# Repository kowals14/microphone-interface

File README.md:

# USB Microphone Interface
This repository holds all the necessary files for [team 12's ECE 477 project](https://engineering.purdue.edu/477grp12/).

## Project Description
Microphone Interface is a microphone interface intended to be used with analog audio microphones. This interface would apply various DSP effects to the audio and pass it to an analog output. Specifically, our device will implement the following functionality:
* Be powered via micro-USB.
* Receive an analog audio input via 3.5mm TRS jack.
* Apply the following user selectable and user controllable DSP effects:
    * Five band equalization
    * Distortion
    * Delay
*  Allow the user to navigate backwards and formwards via two push buttons.
*   Allow the user to manipulate the following DSP parameters via three rotary encoders:
    * Equalization (for each band):
      * Frequency
      * Width
      * Gain
    * Distortion:
      * Pre-Amp
      * Gain
      * Mix
    * Delay:
      * Time
      * Feedback
      * Mix
* Display the states of each DSP parameter (with a separate page for each effect) via a graphical user interface.
* Output the modified audio signal via a 3.5mm TRS jack.
  
## PROJECT SPECIFIC DESIGN REQUIREMENTS (PSDRS):
* PSDR #1 (Hardware): An ability to send and receive an audio signal to and from a codec and a microcontroller via I2S.
* PSDR #2 (Software): An ability to apply five band EQ, distortion, and delay effects via DSP on an input audio.
* PSDR #3 (Hardware): An ability to control DSP parameters using input to a microcontroller from a set of rotary encoders and buttons.
* PSDR #4 (Hardware): An ability for the microcontroller to interface with an LCD display via SPI.
* PSDR #5 (Software): An ability to provide a GUI to display DSP parameters and corresponding audio effects.

## STRETCH PSDRS:
* PSDR #6 (hardware): An ability to control parameters and interact with the user interface via capacitive touch screen.

## Files
* Final - STM32 Cube project containing the final version of the project.
* Current - Folder containing schematic and pcb files for Kicad

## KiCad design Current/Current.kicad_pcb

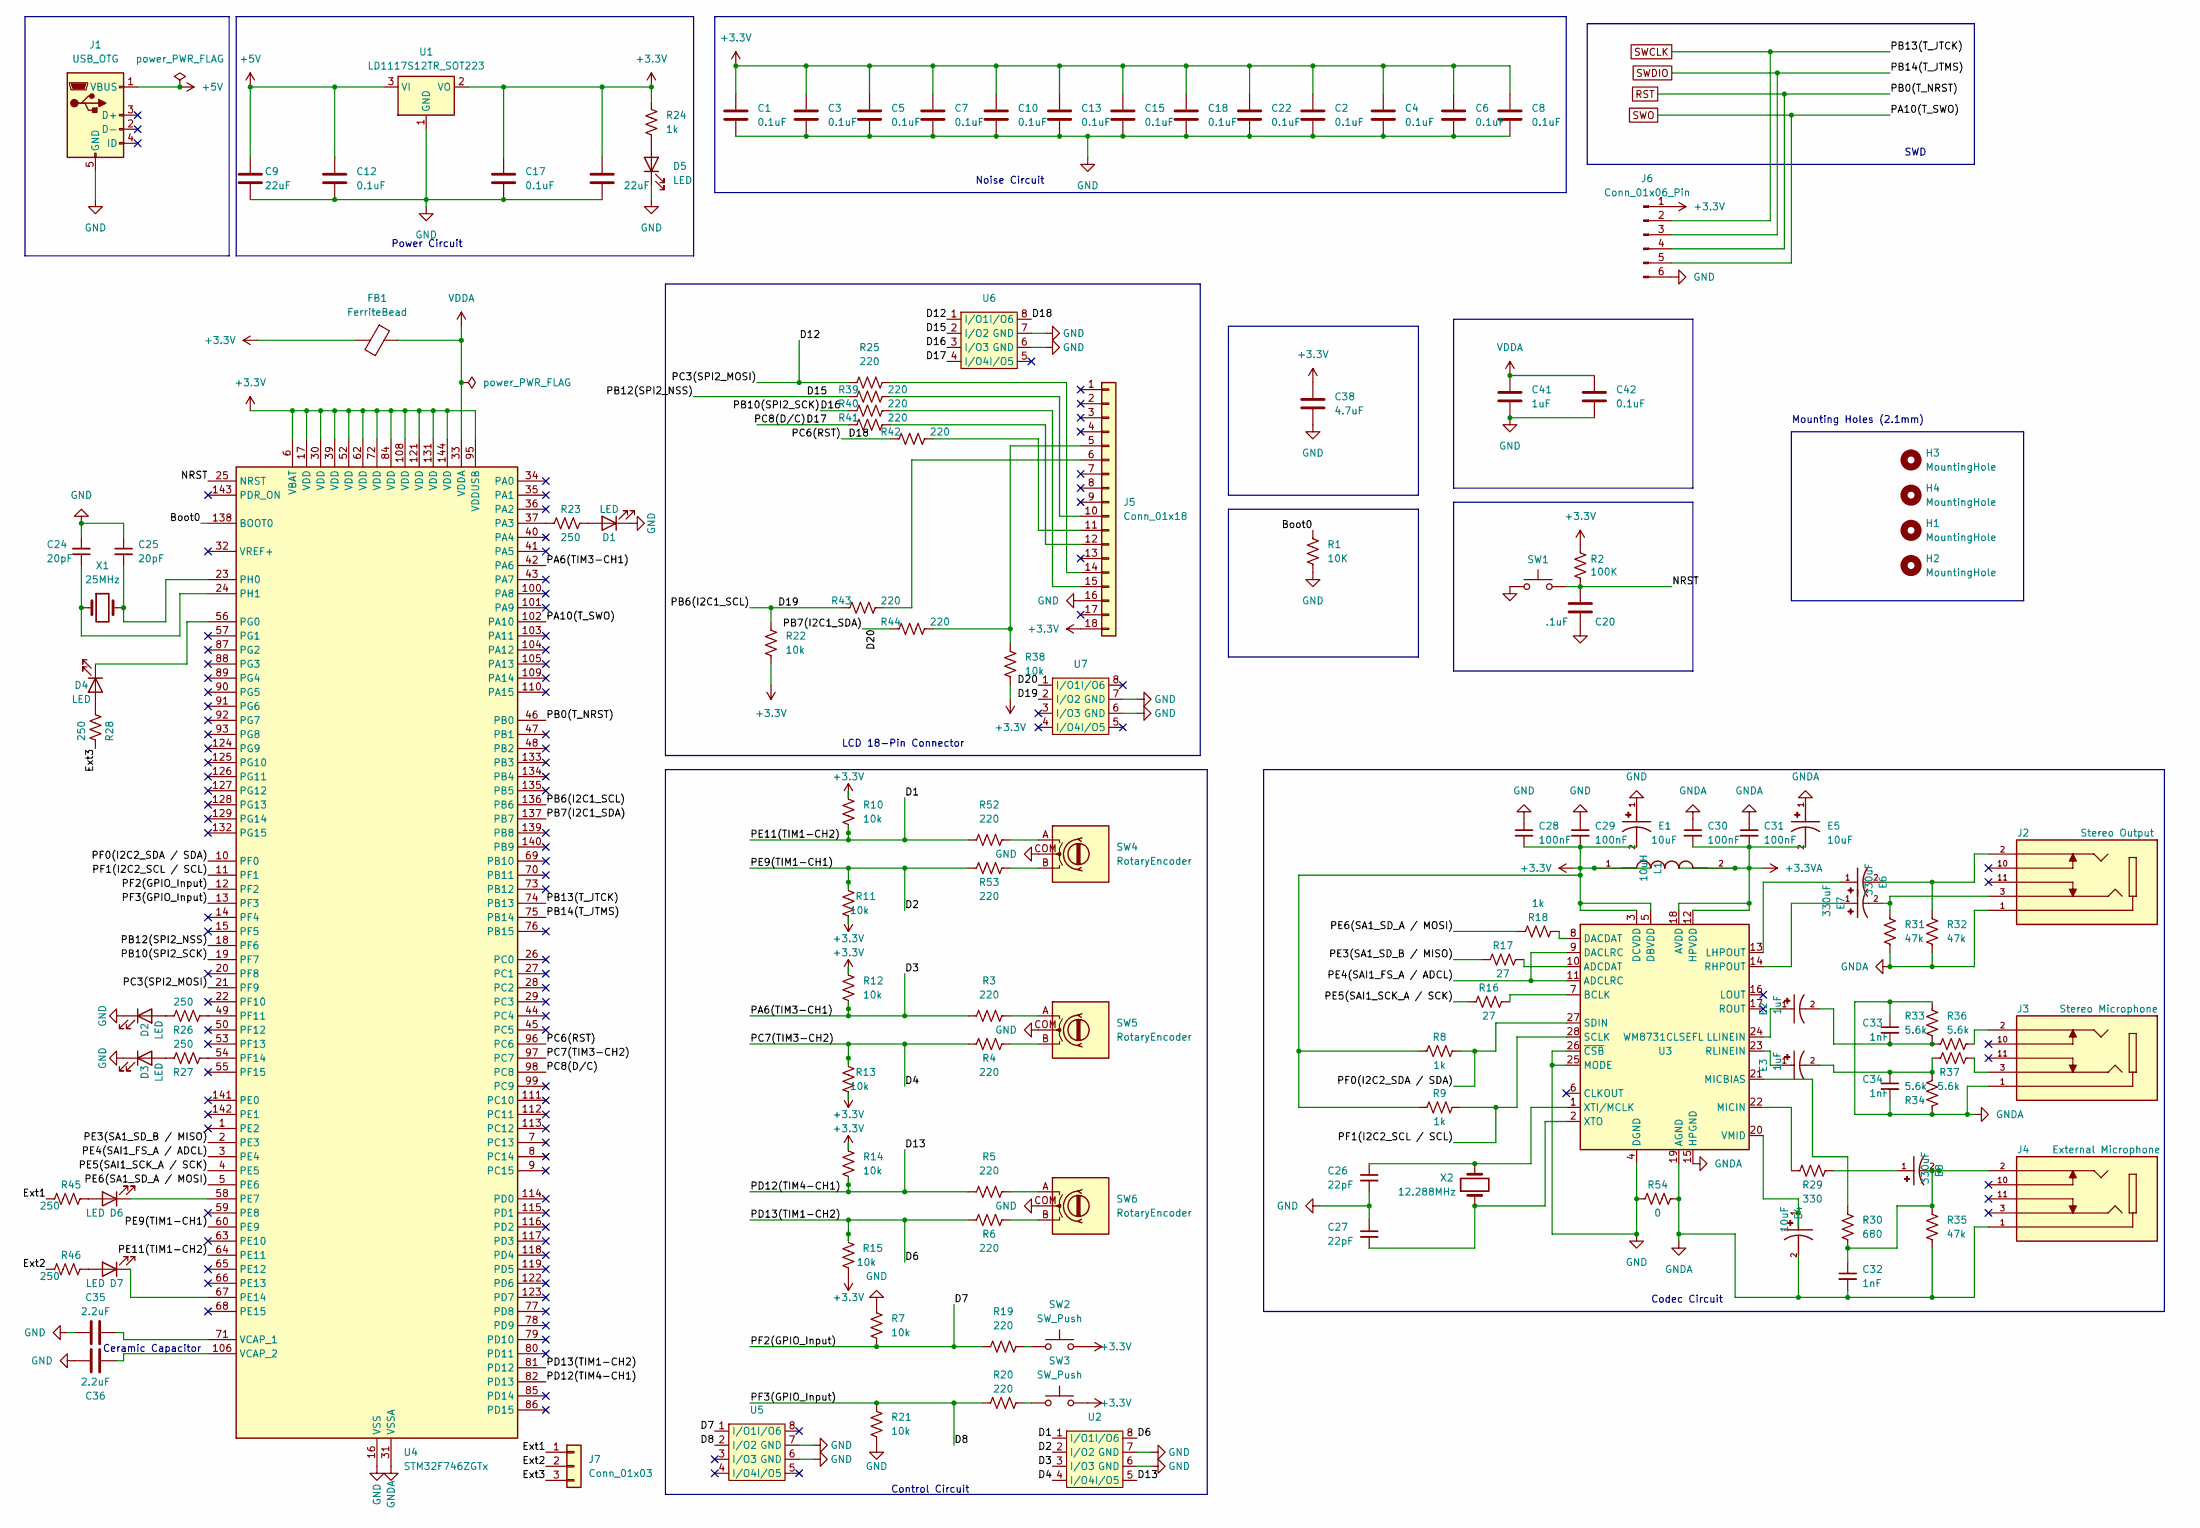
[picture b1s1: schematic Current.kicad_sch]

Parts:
C1, C2, C3, C4, C5, C6, C7, C8, C10, C12, C13, C15, C17, C18, C22, C42: 0.1uF; C_0805_2012Metric
C9, C21: 22uF; C_0805_2012Metric
C20: .1uF; C_0805_2012Metric
C24, C25: 20pF; C_0805_2012Metric
C26, C27: 22pF; C_0805_2012Metric
C28, C29, C30, C31: 100nF; C_0805_2012Metric
C32, C33, C34: 1nF; C_0805_2012Metric
C35, C36: 2.2uF; C_0805_2012Metric
C38: 4.7uF; C_0805_2012Metric
C41: 1uF; C_0805_2012Metric
D1, D2, D3, D4, D5, D6, D7: LED; LED_0805_2012Metric
E1, E4, E5: 10uF; CAPPM3528X210N; PARTREV N/A
E2, E3: 1uF; CAP_EEEFC1V1R0R; PARTREV 10-Oct-19
E6, E7, E8: 330uF; CAP_EEEFT0J331AP; PARTREV 10-Oct-19
FB1: FerriteBead; BEADC1608X75N
H1, H2, H3, H4: MountingHole; MountingHole_4.5mm
J1: USB_OTG; AMPHENOL_10118193-0001LF
J2: Stereo Output; CUI_SJ1-3515-SMT; PARTREV 1.05
J3: Stereo Microphone; CUI_SJ1-3515-SMT; PARTREV 1.05
J4: External Microphone; CUI_SJ1-3515-SMT; PARTREV 1.05
J5: Conn_01x18; CON_527461871_MOL
J6: Conn_01x06_Pin; PinSocket_1x06_P2.54mm_Vertical
J7: Conn_01x03; PinSocket_1x03_P2.54mm_Vertical
L1: 10uH; IND_SLF7045T-100M1R3-PF; PARTREV N/A
R1: 10K; R_0805_2012Metric
R2: 100K; R_0805_2012Metric
R3, R4, R5, R6, R19, R20, R25, R39, R40, R41, R42, R43, R44, R52, R53: 220; R_0805_2012Metric
R7, R10, R11, R12, R13, R14, R15, R21, R22, R38: 10k; R_0805_2012Metric
R8, R9, R18, R24: 1k; R_0805_2012Metric
R16, R17: 27; R_0805_2012Metric
R23, R26, R27, R28, R45, R46: 250; R_0805_2012Metric
R29: 330; R_0805_2012Metric
R30: 680; R_0805_2012Metric
R31, R32, R35: 47k; R_0805_2012Metric
R33, R34, R36, R37: 5.6k; R_0805_2012Metric
R54: 0; R_0805_2012Metric
SW1, SW2, SW3: SW_Push; SW_B3F-4050
SW4, SW5, SW6: RotaryEncoder; XDCR_PEC11R-4215F-S0024
U1: LD1117S12TR_SOT223; SOT-223-3_TabPin2
U2, U5, U6, U7: SO-8_3.9x4.9mm_P1.27mm
U3: WM8731CLSEFL; QFN-28-1EP_5x5mm_P0.5mm_EP3.35x3.35mm
U4: STM32F746ZGTx; LQFP-144_20x20mm_P0.5mm
X1: 25MHz; XTAL_ABM7-25.000MHZ-D2Y-T
X2: 12.288MHz; XTAL_HCM4924000000ABJT

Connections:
+3.3V: C1.1, C2.1, C3.1, C4.1, C5.1, C6.1, C7.1, C8.1, C10.1, C13.1, C15.1, C17.1, C18.1, C21.1, C22.1, C28.2, C29.2, C38.1, E1.2, FB1.2, J5.18, J6.1, L1.1, R2.1, R8.1, R9.1, R10.1, R11.1, R12.1, R13.1, R14.1, R15.1, R22.1, R24.2, R38.1, SW2.2, SW3.2, U1.2 (VO), U3.3 (DCVDD), U3.5 (DBVDD), U4.6 (VBAT), U4.17 (VDD), U4.30 (VDD), U4.39 (VDD), U4.52 (VDD), U4.62 (VDD), U4.72 (VDD), U4.84 (VDD), U4.95 (VDDUSB), U4.108 (VDD), U4.121 (VDD), U4.131 (VDD), U4.144 (VDD)
+3.3VA: C30.2, C31.2, E5.2, L1.2, U3.12 (HPVDD), U3.18 (AVDD)
+5V: C9.1, C12.1, J1.1 (VBUS), U1.3 (VI)
/Boot0: R1.1, U4.138 (BOOT0)
/D1: R10.2, R52.1, U2.1 (I/O1), U4.64 (PE11)
/D2: R11.2, R53.1, U2.2 (I/O2), U4.60 (PE9)
/D3: R3.1, R12.2, U2.3 (I/O3), U4.42 (PA6)
/D4: R4.1, R13.2, U2.4 (I/O4), U4.97 (PC7)
/D6: R6.1, R15.2, U2.8 (I/O6), U4.81 (PD12)
/D7: R7.1, R19.1, U4.12 (PF2), U5.1 (I/O1)
/D8: R20.1, R21.2, U4.13 (PF3), U5.2 (I/O2)
/D12: R25.1, U4.21 (PF9), U6.1 (I/O1)
/D13: R5.1, R14.2, U2.5 (I/O5), U4.82 (PD13)
/D15: R39.1, U4.18 (PF6), U6.2 (I/O2)
/D16: R40.1, U4.19 (PF7), U6.3 (I/O3)
/D17: R41.1, U4.98 (PC8), U6.4 (I/O4)
/D18: R42.1, U4.96 (PC6), U6.8 (I/O6)
/D19: R22.2, R43.1, U4.136 (PB6), U7.2 (I/O2)
/D20: R44.1, U4.137 (PB7), U7.1 (I/O1)
/Ext1: J7.1, R45.2
/Ext2: J7.2, R46.2
/Ext3: J7.3, R28.1
/NRST: C20.1, R2.2, SW1.2, U4.25 (NRST)
/PE3(SA1_SD_B / MISO): R17.2, U4.2 (PE3)
/PE4(SAI1_FS_A / ADCL): U3.9 (DACLRC), U3.11 (ADCLRC), U4.3 (PE4)
/PE5(SAI1_SCK_A / SCK): R16.2, U4.4 (PE5)
/PE6(SA1_SD_A / MOSI): R18.2, U4.5 (PE6)
/PF0(I2C2_SDA / SDA): R8.2, U3.27 (SDIN), U4.10 (PF0)
/PF1(I2C2_SCL / SCL): R9.2, U3.28 (SCLK), U4.11 (PF1)
GND: C1.2, C2.2, C3.2, C4.2, C5.2, C6.2, C7.2, C8.2, C9.2, C10.2, C12.2, C13.2, C15.2, C17.2, C18.2, C20.2, C21.2, C22.2, C24.2, C25.1, C26.2, C27.1, C28.1, C29.1, C35.1, C36.1, C38.2, C41.2, C42.2, D1.1 (K), D2.1 (K), D3.1 (K), D5.1 (K), E1.1, J1.5 (GND), J5.16, J6.6, R1.2, R7.2, R21.1, R54.1, SW1.1, SW4.COM (C), SW5.COM (C), SW6.COM (C), U1.1 (GND), U2.6 (GND), U2.7 (GND), U3.4 (DGND), U3.25 (MODE), U3.26 (~CSB), U4.16 (VSS), U4.38 (VSS), U4.51 (VSS), U4.61 (VSS), U4.83 (VSS), U4.94 (VSS), U4.107 (VSS), U4.120 (VSS), U4.130 (VSS), U5.6 (GND), U5.7 (GND), U6.6 (GND), U6.7 (GND), U7.6 (GND), U7.7 (GND)
GNDA: C30.1, C31.1, C32.2, C33.1, C34.2, E4.2, E5.1, J2.1, J3.1, J4.1, R31.2, R32.2, R33.1, R34.1, R35.2, R54.2, U3.15 (HPGND), U3.19 (AGND), U3.29 (AGND), U4.31 (VSSA)
unnamed: C32.1, E8.2, J4.2, R30.2, R35.1
unnamed: C33.2, E2.2, R33.2, R36.2
unnamed: C34.1, E3.2, R34.2, R37.1
unnamed: D1.2 (A), R23.1
unnamed: D2.2 (A), R26.1
unnamed: D3.2 (A), R27.1
unnamed: D4.2 (A), R28.2
unnamed: D4.1 (K), U4.56 (PG0)
unnamed: D5.2 (A), R24.1
unnamed: D6.2 (A), R45.1
unnamed: D6.1 (K), U4.58 (PE7)
unnamed: D7.2 (A), R46.1
unnamed: D7.1 (K), U4.67 (PE14)
unnamed: E6.2, J2.2, R32.1
unnamed: E7.2, J2.3, R31.1
unnamed: E8.1, R29.2
unnamed: J3.2, R36.1
unnamed: J3.3, R37.2
unnamed: J5.5, R38.2, R44.2
unnamed: J5.6, R43.2
unnamed: J5.10, R39.2
unnamed: J5.11, R42.2
unnamed: J5.12, R41.2
unnamed: J5.14, R25.2
unnamed: J5.15, R40.2
unnamed: R3.2, SW5.A
unnamed: R4.2, SW5.B
unnamed: R5.2, SW6.A
unnamed: R6.2, SW6.B
unnamed: R19.2, SW2.1
unnamed: R20.2, SW3.1
unnamed: R52.2, SW4.A
unnamed: R53.2, SW4.B
unnamed: R17.1, U3.10 (ADCDAT)
unnamed: R16.1, U3.7 (BCLK)
unnamed: R18.1, U3.8 (DACDAT)
unnamed: E6.1, U3.13 (LHPOUT)
unnamed: E2.1, U3.24 (LLINEIN)
unnamed: R30.1, U3.21 (MICBIAS)
unnamed: R29.1, U3.22 (MICIN)
unnamed: E7.1, U3.14 (RHPOUT)
unnamed: E3.1, U3.23 (RLINEIN)
unnamed: E4.1, U3.20 (VMID)
unnamed: C26.1, U3.1 (XTI/MCLK), X2.2
unnamed: C27.2, U3.2 (XTO), X2.1
unnamed: R23.2, U4.37 (PA3)
unnamed: R26.2, U4.49 (PF11)
unnamed: R27.2, U4.54 (PF14)
unnamed: C25.2, U4.23 (PH0), X1.2
unnamed: C24.1, U4.24 (PH1), X1.1
unnamed: C35.2, U4.71 (VCAP_1)
unnamed: C36.2, U4.106 (VCAP_2)
RST: J6.4, U4.46 (PB0)
SWCLK: J6.2, U4.74 (PB13)
SWDIO: J6.3, U4.75 (PB14)
SWO: J6.5, U4.102 (PA10)
VDDA: C41.1, C42.1, FB1.1, U4.33 (VDDA)

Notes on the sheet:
Ceramic Capacitor
Control Circuit
LCD 18-Pin Connector
Mounting Holes (2.1mm)
Power Circuit
Codec Circuit
Noise Circuit
SWD

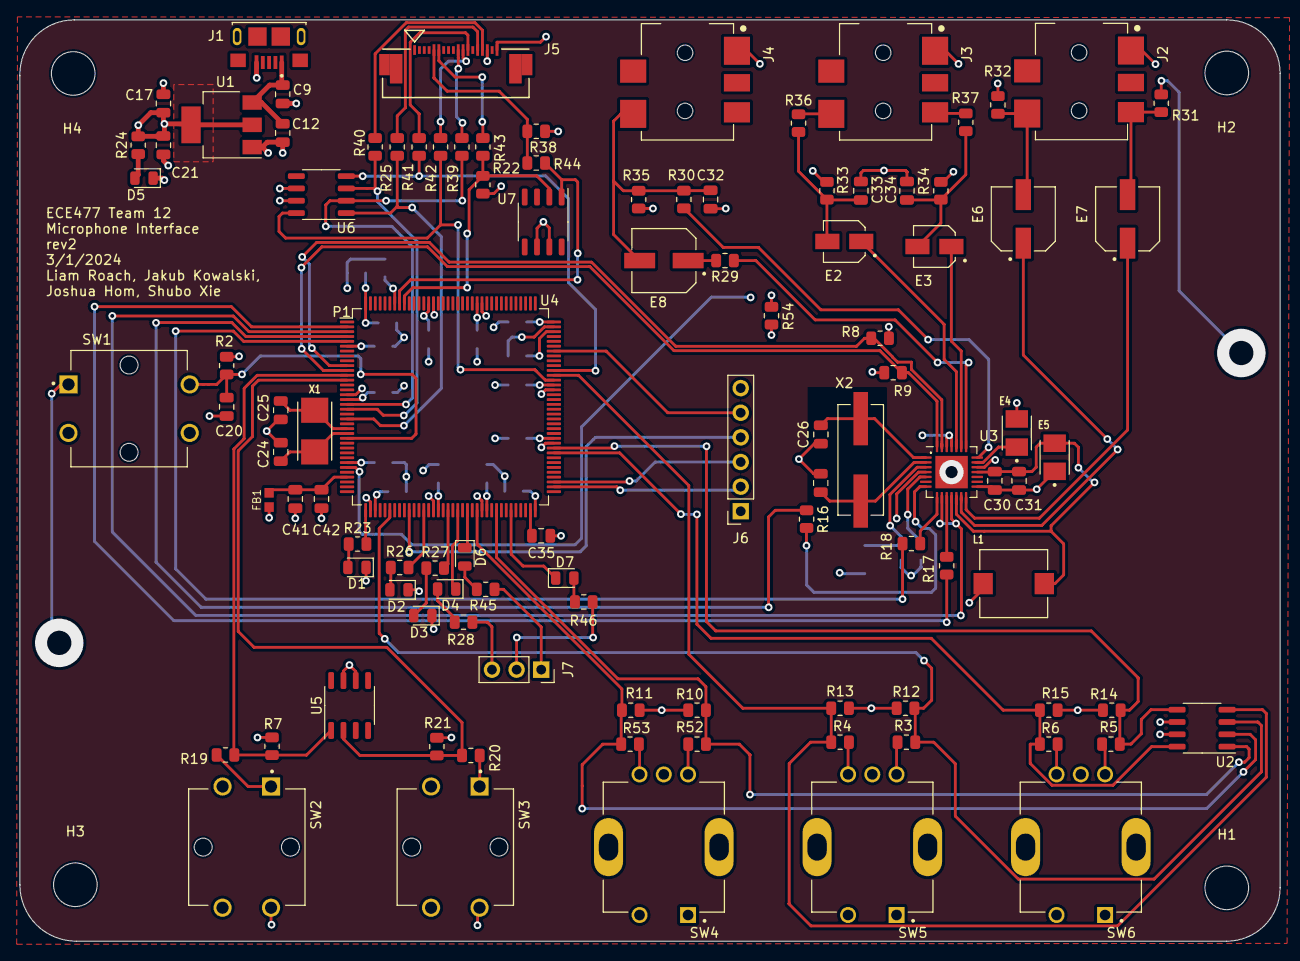
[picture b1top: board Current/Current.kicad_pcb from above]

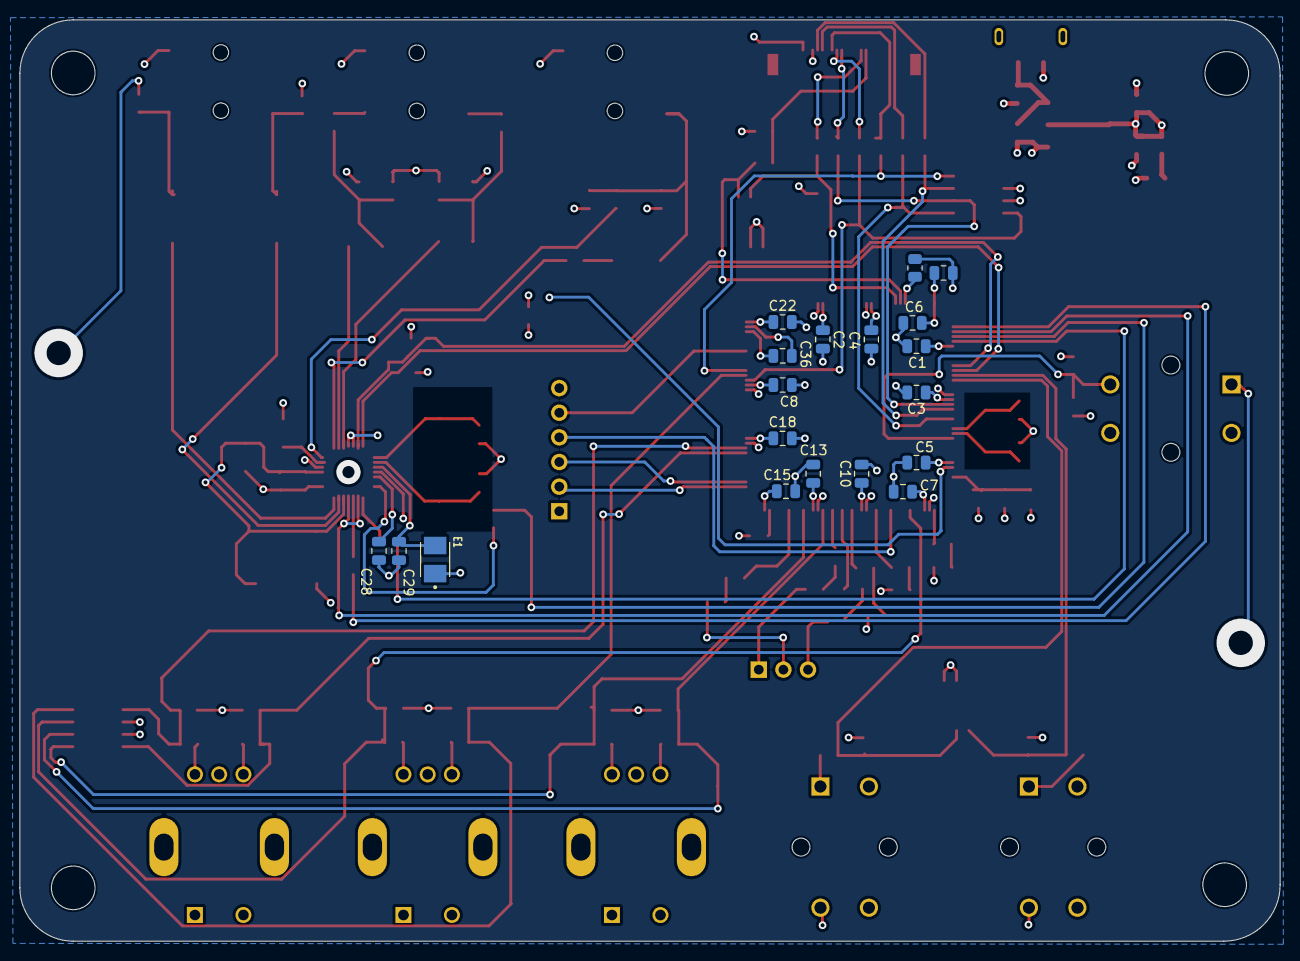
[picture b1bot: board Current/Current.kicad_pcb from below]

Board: 4 copper layers, 129.9 x 95.0 mm, 126 parts (19 on the bottom side), 88 nets.

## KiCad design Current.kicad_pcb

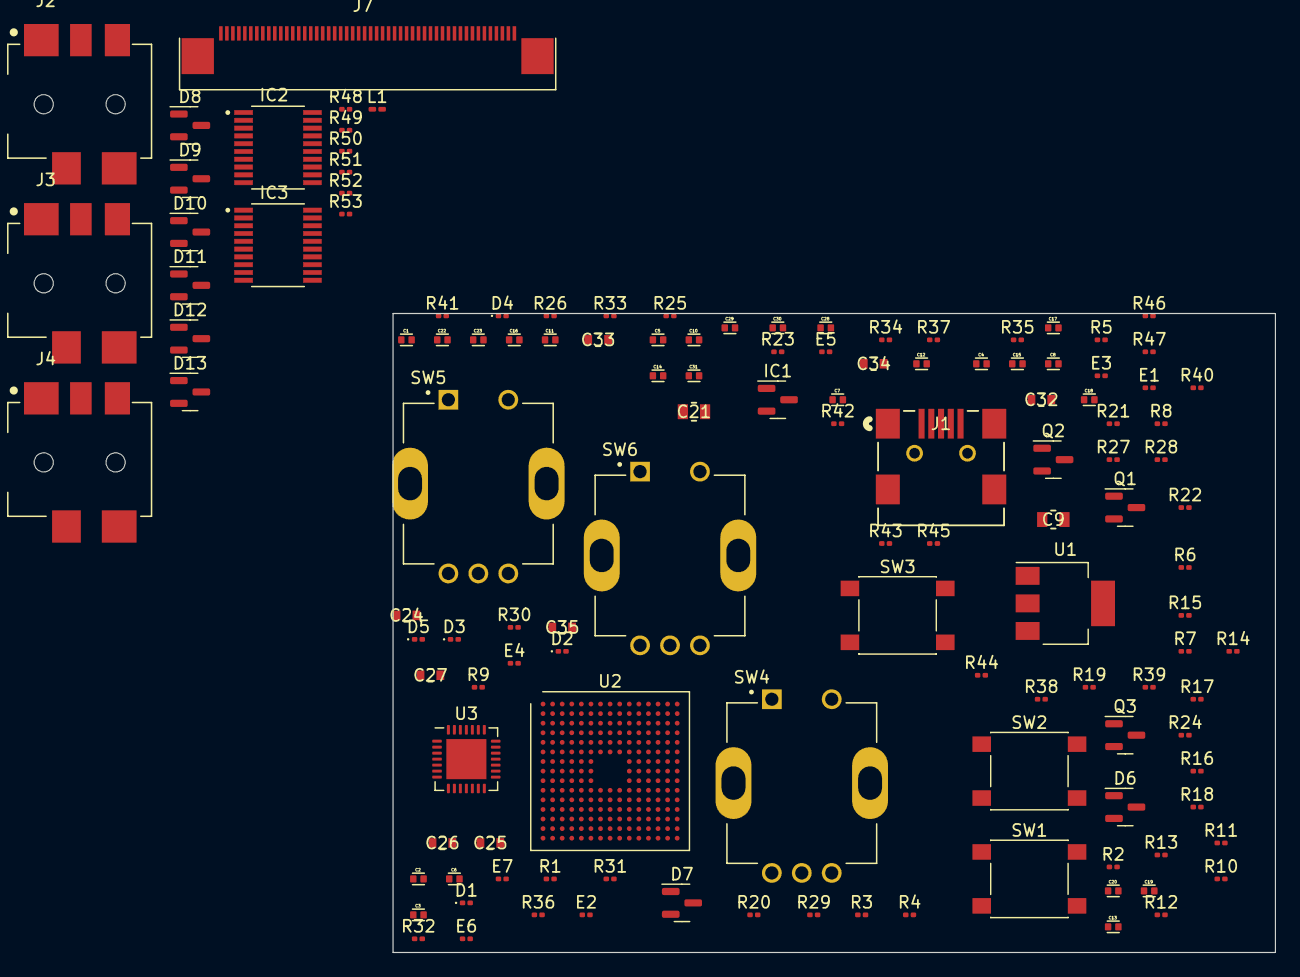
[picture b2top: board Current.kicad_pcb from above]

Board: 2 copper layers, 73.7 x 53.3 mm, 129 parts (0 on the bottom side), 78 nets, no tracks yet.

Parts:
C1, C2, C3, C4, C5, C6, C7, C8, C10, C11, C12, C13, C14, C15, C16, C17, C18, C19, C22, C23: 0.1uF
C9, C21: 22uF
C20: .1uF; 0.1uF
C24, C25: 20pF
C26, C27: 22pF; 20pF
C28, C29, C30, C31: 100nF; 0.1uF
C32, C33, C34, C35: 1nF; 1000pF
D1, D2, D3, D4, D5: LED; LED_0201_0603Metric
D6, D7, D8, D9, D10, D11, D12, D13: BZX84Cxx; SOT-23
E1, E4, E5: 10uF; C_0201_0603Metric
E2, E3: 220uF; C_0201_0603Metric
E6, E7: 330uF; C_0201_0603Metric
IC1: LM809; SOT-23
IC2, IC3: 74HC245; SOP65P640X120-20N
J1: USB_OTG; usb_mini
J2: Stereo Output; CUI_SJ1-3515-SMT
J3: Stereo Microphone; CUI_SJ1-3515-SMT
J4: External Microphone; CUI_SJ1-3515-SMT
J7: Conn_01x50_Pin; 68715014522
L1: 10uH; L_0201_0603Metric_Pad0.64x0.40mm_HandSolder
Q1, Q2, Q3: BSS138; SOT-23
R1, R23, R26: 10K; R_0201_0603Metric
R2: 100K; R_0201_0603Metric
R3, R4, R5, R6, R7: 150; R_0201_0603Metric
R8, R9, R10, R11, R12, R13, R14, R15, R18, R38: 1k; R_0201_0603Metric
R16, R17: 27; R_0201_0603Metric
R19, R20, R48, R49, R50, R51, R52, R53: 220; R_0201_0603Metric
R21, R22, R27, R28, R40, R41, R46, R47: 10k; R_0201_0603Metric
R24, R25: R_Small; R_0201_0603Metric
R29: 330; R_0201_0603Metric
R30: 680; R_0201_0603Metric
R31, R32, R35: 47k; R_0201_0603Metric
R33, R34, R36, R37: 5.6k; R_0201_0603Metric
R39: 2.2k; R_0201_0603Metric
R42, R44, R45: 10; R_0201_0603Metric
R43: 1; R_0201_0603Metric
SW1, SW2, SW3: SW_Push; SW_SPST_PTS645
SW4, SW5, SW6: RotaryEncoder; rotary_encoder
U1: LD1117S12TR_SOT223; SOT-223-3_TabPin2
U2: STM32F746NGHx; TFBGA-216_13x13mm_Layout15x15_P0.8mm
U3: WM8731CLSEFL; QFN-28-1EP_5x5mm_P0.5mm_EP3.35x3.35mm

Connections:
+3.3V: C1.1, C1.2, C2.1, C2.2, C3.1, C3.2, C4.1, C4.2, C5.1, C5.2, C6.1, C6.2, C7.1, C7.2, C8.1, C8.2, C9.2, C10.1, C10.2, C11.1, C11.2, C12.2, C13.1, C13.2, C14.1, C14.2, C15.1, C15.2, C16.1, C16.2, C17.1, C17.2, C18.1, C18.2, C19.1, C19.2, C20.2, C21.1, C21.2, C22.1, C22.2, C23.1, C23.2, C24.2, C25.1, C26.2, C27.1, C28.1, C29.1, C30.1, C31.1, C32.2, C33.1, C34.2, D1.1 (K), D2.1 (K), D3.1 (K), D4.1 (K), D5.1 (K), D6.1 (A), D7.1 (A), D8.1 (A), D9.1 (A), D10.1 (A), D11.1 (A), D12.1 (A), D13.1 (A), E1.1, E4.2, E5.1, IC1.1 (GND), IC2.10 (GND), IC2.19 (CE), IC3.10 (GND), IC3.19 (CE), J1.5 (GND), J1.6 (Shield), J7.43, J7.48, J7.49, J7.50, Q3.2 (S), R1.2, R2.1, R24.2, R25.1, R26.2, R31.2, R32.2, R33.1, R34.1, R35.2, R40.2, R41.2, R46.1, R47.1, SW1.1, U1.1 (GND), U1.2 (VO), U2.C1 (VBAT), U2.E7 (VDD), U2.E8 (VDD), U2.E9 (VDD), U2.E10 (VDD), U2.F2 (VSS), U2.F4 (VDD), U2.F5 (VDD), U2.F6 (VSS), U2.F7 (VSS), U2.F8 (VSS), U2.F9 (VSS), U2.F10 (VSS), U2.F11 (VDD), U2.G5 (VDD), U2.G6 (VSS), U2.G10 (VSS), U2.H5 (VDD), U2.H6 (VSS), U2.H10 (VSS), U2.H11 (VDD), U2.J5 (VDD), U2.J6 (VSS), U2.J10 (VSS), U2.J11 (VDD), U2.K5 (VDD), U2.K6 (VSS), U2.K7 (VSS), U2.K8 (VSS), U2.K9 (VSS), U2.K10 (VSS), U2.K11 (VDD), U2.L6 (VSS), U2.L7 (VDD), U2.L8 (VDD), U2.L9 (VDD), U2.L10 (VDD), U2.M1 (VSSA), U2.R1 (VDDA), U3.4 (DGND), U3.15 (HPGND), U3.19 (AGND), U3.25 (MODE), U3.26 (~CSB), U3.29 (AGND)
+5V: C9.1, C12.1, J1.1 (VBUS), R21.1, R22.1, R27.1, R28.1, R38.1, U1.3 (VI)
/CTP_IRQ: J7.46, U2.A8 (PB5)
/IM0: J7.6, R47.2
/IM1: J7.7, R46.2
/IM2: J7.8, R41.1
/IM3: J7.9, R40.1
/LCD_CS: IC2.15 (B3), J7.38
/LCD_CS_5V: IC2.5 (A3), R7.2, U2.F14 (PC9)
/LCD_RD: IC2.12 (B6), J7.35
/LCD_RD_5V: IC2.8 (A6), IC3.1 (A->B), R26.1
/LCD_RS: IC2.14 (B4), J7.37
/LCD_RST: IC2.11 (B7), J7.10, J7.47
/LCD_RST_5V: IC1.2 (~RESET), IC2.9 (A7), R5.2, R23.2, U2.H15 (PC6)
/LCD_RS_5V: IC2.6 (A4), R3.2, U2.P12 (PB10)
/LCD_WR: IC2.13 (B5), J7.36
/LCD_WR_5V: IC2.7 (A5), R6.2, U2.G14 (PC8)
/LEDA: J7.2, J7.3, J7.4, J7.5, R42.2, R43.2, R44.2, R45.2
/LEDK: J7.1, Q3.3 (D)
/PA6(TIM3-CH1): R12.2, R50.1, U2.P3 (PA6)
/PC3: IC2.4 (A2), R4.2, U2.L4 (PC3)
/PC7(TIM3-CH2): R13.2, R51.1, U2.G15 (PC7)
/PD12(TIM4-CH1): R14.2, R48.1, U2.M10 (PD12)
/PD13(TIM1-CH2): R15.2, R49.1, U2.M11 (PD13)
/PE3(SA1_SD_B / MISO): R17.2, U2.A2 (PE3)
/PE4(SAI1_FS_A / ADCL): U2.A1 (PE4), U3.9 (DACLRC), U3.11 (ADCLRC)
/PE5(SAI1_SCK_A / SCK): R16.2, U2.B1 (PE5)
/PE6(SA1_SD_A / MOSI): R18.2, U2.B2 (PE6)
/PE9(TIM1-CH1): R10.2, R52.1, U2.N9 (PE8), U2.P9 (PE9)
/PE11(TIM1-CH2): R11.2, R53.1, U2.P10 (PE11), U2.R9 (PE10)
/PF0(I2C2_SDA / SDA): R8.2, U2.D2 (PF0), U3.27 (SDIN)
/PF1(I2C2_SCL / SCL): R9.2, U2.E2 (PF1), U3.28 (SCLK)
/PF2(GPIO_Input): SW2.1, U2.G2 (PF2)
/PF3(GPIO_Input): SW3.1, U2.H2 (PF3)
/SCL_3V: J7.44, Q2.2 (S), R27.2
/SCL_5V: Q2.3 (D), R21.2, U2.B6
/SDA_3V: J7.45, Q1.3 (D), R28.2
/SDA_5V: Q1.2 (S), R22.2, U2.B5 (PB7)
/SDI: IC2.16 (B2), J7.34
/VCC-3.3: C28.2, C29.2, E1.2, L1.1, R8.1, R9.1, U3.3 (DCVDD), U3.5 (DBVDD)
/VCCA-3.3: C30.2, C31.2, E5.2, L1.2, U3.12 (HPVDD), U3.18 (AVDD)
unnamed: C32.1, C35.2, R30.2, R35.1
unnamed: C33.2, E2.2, R33.2, R36.2
unnamed: C34.1, E3.2, R34.2, R37.1
unnamed: C35.1, R29.2
unnamed: D1.2 (A), R3.1
unnamed: D2.2 (A), R4.1
unnamed: D3.2 (A), R5.1
unnamed: D4.2 (A), R6.1
unnamed: D5.2 (A), R7.1
unnamed: D6.3 (K), R19.1, SW2.2
unnamed: D7.3 (K), R20.1, SW3.2
unnamed: D8.3 (K), R48.2, SW6.A
unnamed: D9.3 (K), R49.2, SW6.B
unnamed: D10.3 (K), R50.2, SW5.A
unnamed: D11.3 (K), R51.2, SW5.B
unnamed: D12.3 (K), R52.2, SW4.A
unnamed: D13.3 (K), R53.2, SW4.B
unnamed: E6.2, R32.1
unnamed: E7.2, R31.1
unnamed: Q3.1 (G), R38.2, R39.1
unnamed: R1.1, U2.E6 (BOOT0)
unnamed: C20.1, R2.2, SW1.2, U2.J1 (NRST)
unnamed: C25.2, U2.G1 (PH0)
unnamed: C24.1, U2.H1
unnamed: R17.1, U3.10 (ADCDAT)
unnamed: R16.1, U3.7 (BCLK)
unnamed: R18.1, U3.8 (DACDAT)
unnamed: E6.1, U3.13 (LHPOUT)
unnamed: E2.1, U3.24 (LLINEIN)
unnamed: R30.1, U3.21 (MICBIAS)
unnamed: R29.1, U3.22 (MICIN)
unnamed: E7.1, U3.14 (RHPOUT)
unnamed: E3.1, U3.23 (RLINEIN)
unnamed: E4.1, U3.20 (VMID)
unnamed: C26.1, U3.1 (XTI/MCLK)
unnamed: C27.2, U3.2 (XTO)
VCC: IC1.3 (VCC), IC2.1 (A->B), IC2.20 (VCC), IC3.20 (VCC), J7.40, J7.41, J7.42, Q1.1 (G), Q2.1 (G), R10.1, R11.1, R12.1, R13.1, R14.1, R15.1, R19.2, R20.2, R23.1, R24.1, R25.2, R39.2, R42.1, R43.1, R44.1, R45.1

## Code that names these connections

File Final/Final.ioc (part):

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Mcu.Name=STM32F746ZGTx
Mcu.Package=LQFP144
Mcu.UserName=STM32F746ZGTx
PA13.Mode=Serial_Wire
PA13.Signal=SYS_JTMS-SWDIO
PA14.Mode=Serial_Wire
PA14.Signal=SYS_JTCK-SWCLK
PA3.GPIOParameters=GPIO_Label
PA3.GPIO_Label=LED1
PA3.Signal=GPIO_Output
PA6.Signal=S_TIM3_CH1
PB6.GPIOParameters=GPIO_Pu
PB6.GPIO_Pu=GPIO_PULLUP
PB6.Mode=I2C
PB6.Signal=I2C1_SCL
PB7.GPIOParameters=GPIO_Pu
PB7.GPIO_Pu=GPIO_PULLUP
PB7.Mode=I2C
PB7.Signal=I2C1_SDA
PC3.Signal=SPI2_MOSI
PC6.GPIOParameters=GPIO_Label
PC6.GPIO_Label=RST
PC6.Signal=GPIO_Output
PC7.Signal=S_TIM3_CH2
PC8.GPIOParameters=GPIO_Label
PC8.GPIO_Label=D/C
PC8.Signal=GPIO_Output
PD12.Signal=S_TIM4_CH1
PD13.Signal=S_TIM4_CH2
PE11.Signal=S_TIM1_CH2
PE3.Mode=SAI_B_SyncSlave
PE3.Signal=SAI1_SD_B
PE4.Mode=SAI_A_AsyncSlave
PE4.Signal=SAI1_FS_A
PE5.Mode=SAI_A_AsyncSlave
PE5.Signal=SAI1_SCK_A
PE6.Mode=SAI_A_AsyncSlave
PE6.Signal=SAI1_SD_A
PE9.Signal=S_TIM1_CH1
PF0.GPIOParameters=GPIO_Pu
PF0.GPIO_Pu=GPIO_NOPULL
PF0.Mode=I2C
PF0.Signal=I2C2_SDA
PF1.GPIOParameters=GPIO_Pu
PF1.GPIO_Pu=GPIO_NOPULL
PF1.Mode=I2C
PF1.Signal=I2C2_SCL
PF11.GPIOParameters=GPIO_Label
PF11.GPIO_Label=LED2
PF11.Signal=GPIO_Output
PF14.GPIOParameters=GPIO_Label
PF14.GPIO_Label=LED3
PF14.Signal=GPIO_Output
PF2.GPIOParameters=GPIO_Label
PF2.GPIO_Label=LeftButton
PF2.Signal=GPIO_Input
PF3.GPIOParameters=GPIO_Label
PF3.GPIO_Label=Right Button
PF3.Signal=GPIO_Input
PF6.Mode=NSS_Signal_Hard_Output
PF6.Signal=SPI5_NSS
PF7.Mode=TX_Only_Simplex_Unidirect_Master
PF7.Signal=SPI5_SCK
PF9.Mode=TX_Only_Simplex_Unidirect_Master
PF9.Signal=SPI5_MOSI
PH0/OSC_IN.Mode=HSE-External-Oscillator
PH0/OSC_IN.Signal=RCC_OSC_IN
PH1/OSC_OUT.Mode=HSE-External-Oscillator
PH1/OSC_OUT.Signal=RCC_OSC_OUT
RCC.HSE_VALUE=24000000
RCC.SYSCLKFreq_VALUE=216000000
RCC.SYSCLKSource=RCC_SYSCLKSOURCE_PLLCLK
board=custom

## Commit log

2024-01-14 Update README.md
    Added project description.
2024-01-14 Update README.md
    Added website link in readme.
2024-01-15 testing commit from local machine
2024-01-24 initial audio_in
2024-01-26 implemented lowpass filter, testing in jupyter notebook
2024-01-28 modfied testing notebook
2024-01-31 fixed lowpass filter, implemented highpass and bandpass
2024-01-31 improved graph output
2024-02-02 setup for delay files
2024-02-02 add arduino codec demos
2024-02-11 edits to file structure
2024-02-11 added working LCD interface project for F746ZG Nucleo
2024-02-11 added README
2024-02-15 add cube project files for codec
2024-02-15 Add files via upload
    Added external oscillator, rough draft of screen circuit, switched out resistor symbols, added control circuit LED's
2024-02-18 LCD Circuit Completed
2024-02-20 fixed timing issues
2024-02-20 Added L/R LINEIN jack for codec
2024-02-20 Added Solder Jumpers to IC1 (PB6/PB7)
2024-02-20 PDF of Current
2024-02-21 Added missing footprints and redid LCD connector
2024-02-22 Added more libraries and organized layout
2024-02-25 PCB layout progress
2024-02-27 Condensed Schematic
2024-02-27 Correct tantalums
2024-02-28 Updated Codec Crystal
2024-02-28 Some traces adjusted
2024-02-28 Traces adjusted
2024-03-05 Added Debugging LED's to Schematic
2024-04-03 4/3/2024
2024-04-10 added in lcd interface w/ encoders
2024-04-11 delay
2024-04-13 refactored audioFX library
2024-04-13 updated the implementation of applying multiple FX
2024-04-14 buffer size fix
2024-04-14 updated audiofx apply functions
2024-04-14 refactoring audiofx library, support for stereo signals
2024-04-15 parameter updating
2024-04-15 -Josh 4/15
2024-04-16 working 5 band eq and distortion
2024-04-16 ui complete, touchscreen navigation, encoder limits, button debouncing
2024-04-18 quality testing
2024-05-14 cleanup
2024-05-14 Revert "cleanup"
    This reverts commit 3fe7bf66a595cfb90ba8a6e7212a57d9f045a3b8.
2024-05-15 unzipped kicad folder
